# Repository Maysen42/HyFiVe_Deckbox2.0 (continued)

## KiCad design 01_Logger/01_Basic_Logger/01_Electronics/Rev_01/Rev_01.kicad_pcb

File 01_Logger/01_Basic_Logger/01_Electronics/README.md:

# Basic Logger - Electronics

The hardware is designed and can be modified in KiCad 7. Therefore the folder **/HyfiveLib** contains custom footprints and schematics for the projects below.

## Main PCB
The main PCB is designed to run the operations of the logger. It features an ESP32 as a micro controller and some peripheral components to integrate a wide range of sensors. To assemble a PCB for a logger follow the instructions of the [BOM.md](./BOM.md). The basic logger can implement sensors by

	- 3x I2C
	- 2x UART
	- 1x RS485

To select possible sensors to implement take a look into the subfolder [*../04_Sensors*](../04_Sensors/). The list can of course be extended. So far all sensors except the ones by BlueRobotics are connected with Molex PicoBlade connectors. How to connect each sensor in hardware is described in the sensor readme.

How to program the electronics after manufacturing is explained in the subfolder [*../03_Software*](../03_Software/).

A basic version of the PCB is shown in the image below.

<figure> 

   <figurecaption><a name="figure1">*Figure 1:*</a> *Main PCB inside the basic logger*</figurecaption>
</figure>

## Keller connector
  
One additional PCB, that is needed to implement a Keller 9LD pressure sensor, is given in **/KellerConnector**. The PCB can be soldered to the pins of the sensor and can then be directly connected to I2C1 (53261-0471) of the main PCB with a 4 pin Molex connector (15134-0402).

<figure> 

   <figurecaption><a name="figure2">*Figure 2:*</a> *Small PCB for interfacing the Keller pressure sensor*</figurecaption>
</figure>

## Battery

The power supply of the logger can be any battery pack that fits the case. We have user 12 LiPo (3,7 V, type 18650) cells in parallel (12P1S) with the connector Molex: 15136-0203. This fits to the power socket of the PCB (55935-0230).

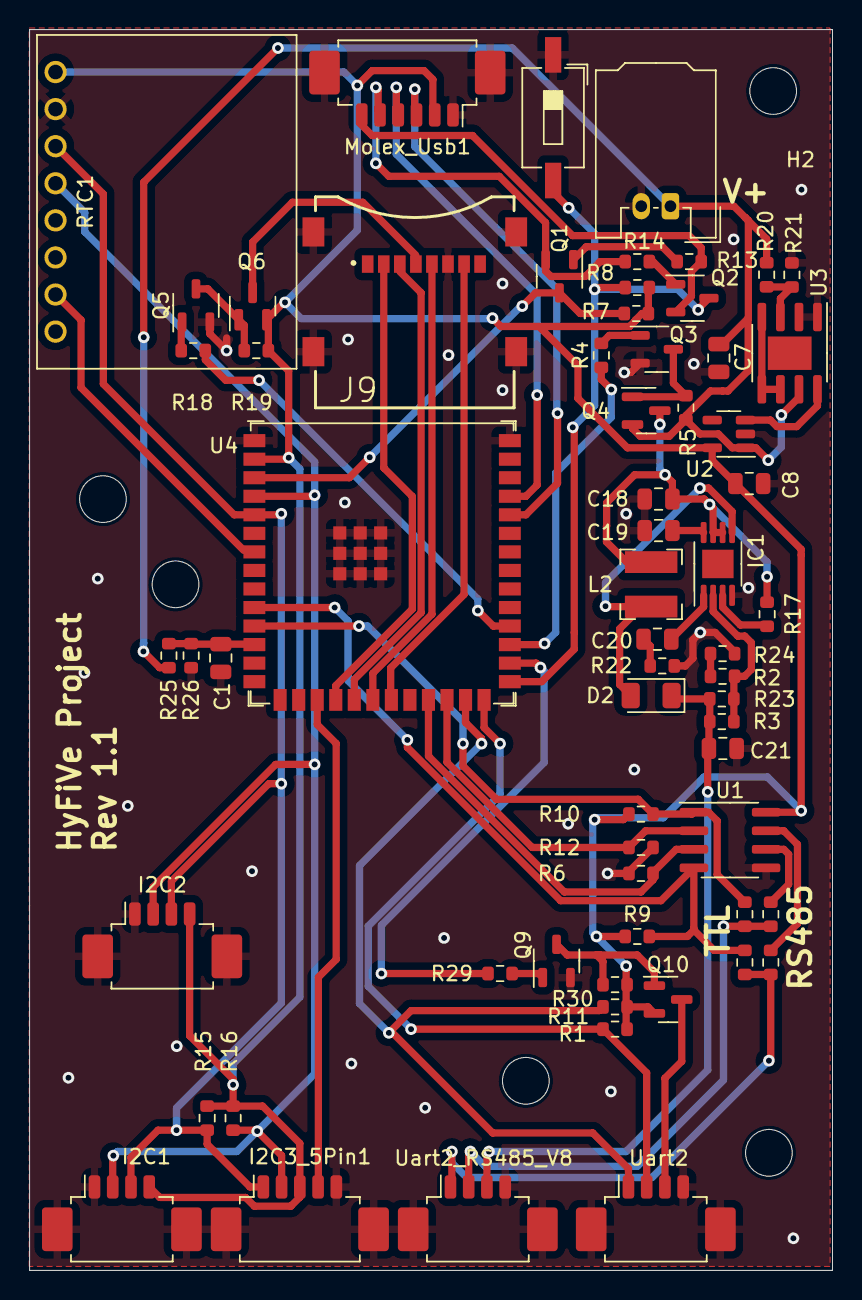
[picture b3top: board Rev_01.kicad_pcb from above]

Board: 2 copper layers, 55.0 x 85.0 mm, 69 parts (0 on the bottom side), 53 nets.

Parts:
C1, C19: 10n; C_0805_2012Metric
C7, C8: 1µ; C_0805_2012Metric
C18: 10µ; C_0805_2012Metric
C20: 2,2n; C_0805_2012Metric
C21: 4,7µ; C_0805_2012Metric
D2: D_Schottky; D_1206_3216Metric
H1, H2, H3: MountingHole; MountingHole_3.2mm_M3
H4, H5: MountingHole; MountingHole_3.2mm_M3_DIN965
I2C1, I2C2: Conn_01x04_MountingPin; Molex_PicoBlade_53261-0471_1x04-1MP_P1.25mm_Horizontal
I2C3_5Pin1: Conn_01x05_MountingPin; Molex_PicoBlade_53261-0571_1x05-1MP_P1.25mm_Horizontal
IC1: MP3213DH-LF-Z; MSOP-8-1EP_3x3mm_P0.65mm_EP1.95x2.15mm
J9: Micro_SD_Card; GCT_MEM2067-02-180-00-A_REVB
L2: 4,7µ; L_Bourns-SRN4018
Molex_Battery1: Conn_01x02; Molex_MicroClasp_55935-0230_1x02_P2.00mm_Horizontal
Molex_Usb1: Conn_01x06_MountingPin; Molex_PicoBlade_53261-0671_1x06-1MP_P1.25mm_Horizontal
Q1, Q2, Q3, Q5, Q9: SS8050-G; SOT-23-3
Q4, Q6, Q10: BSS83P; SOT-23
R1, R9, R10, R11: 100k; R_0603_1608Metric
R2, R24: 12k; R_0603_1608Metric
R3, R23: 470k; R_0603_1608Metric
R4, R5, R17, R18, R19, R22, R29, R30: 15k; R_0603_1608Metric
R6, R12, R15, R16: 1k; R_0603_1608Metric
R7, R8, R13, R14: 10k; R_0603_1608Metric
R20, R21, R25, R26: 1M; R_0603_1608Metric
R40, R41, R42, R43: 0; R_0603_1608Metric
RTC1: Conn_01x08; DS3231Module
SW1: SW_DIP_x01; SW_DIP_SPSTx01_Slide_6.7x4.1mm_W8.61mm_P2.54mm_LowProfile
U1: THVD14x9; SOIC-8_3.9x4.9mm_P1.27mm
U2: RT9080-33GJ5; SOT-23-5
U3: LTC1540; SOIC-8-1EP_3.9x4.9mm_P1.27mm_EP2.29x3mm
U4: ESP32-S3-WROOM-1; ESP32-S3-WROOM-1U
Uart2, Uart2_RS485_V8: Conn_01x04_MountingPin; Molex_PicoBlade_53261-0471_1x04-1MP_P1.25mm_Horizontal

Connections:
/3V3: C8.1, I2C1.4, I2C2.4, I2C3_5Pin1.3, Molex_Usb1.2, Q6.2 (S), Q10.2 (S), R1.1, R7.2, R8.2, R9.1, R10.1, R11.1, R15.2, R16.2, R19.1, R30.1, RTC1.1, U1.8 (VCC), U2.5 (VOUT), U4.2 (3V3)
/AnaIn: C1.1, R25.2, R26.1, U4.12 (GPIO8/TOUCH8/ADC1_CH7/SUBSPICS1)
/BoostEnable: R4.1, U4.29 (SPIIO7/GPIO36/FSPICLK/SUBSPICLK)
/CS_SD: J9.2 (DAT3/CD), U4.18 (GPIO10/TOUCH10/ADC1_CH9/FSPICS0/FSPIIO4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)
/DE485: R6.1, U1.3 (DE), U4.23 (GPIO21)
/DTR: Molex_Usb1.6, Q2.2, R13.1
/EN: Q1.3, R7.1, U4.3 (EN)
/EzoOff: I2C3_5Pin1.4, U4.17 (GPIO9/TOUCH9/ADC1_CH8/FSPIHD/SUBSPIHD)
/IO0: Q2.3, R8.1, SW1.2, U4.27 (GPIO0/BOOT)
/MISO: J9.7 (DAT0), U4.21 (GPIO13/TOUCH13/ADC2_CH2/FSPIQ/FSPIIO7/S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)
/MOSI: J9.3 (CMD), U4.19 (GPIO11/TOUCH11/ADC2_CH0/FSPID/FSPIIO5/S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)
/RE485: R12.1, U1.2 (RE), U4.24 (GPIO47/SPICLK_P/SUBSPICLK_P_DIFF)
/RTS: Molex_Usb1.5, Q1.2, R14.1
/RXD0: Molex_Usb1.3, U4.36 (U0RXD/GPIO44/CLK_OUT2)
/RtcInt: RTC1.7, U4.7 (GPIO7/TOUCH7/ADC1_CH6)
/SCK: J9.5 (CLK), U4.20 (GPIO12/TOUCH12/ADC2_CH1/FSPICLK/FSPIIO6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)
/SCL: I2C1.3, I2C2.3, I2C3_5Pin1.1, R15.1, RTC1.3, U4.5 (GPIO5/TOUCH5/ADC1_CH4)
/SDA: I2C1.2, I2C2.2, I2C3_5Pin1.2, R16.1, RTC1.4, U4.4 (GPIO4/TOUCH4/ADC1_CH3)
/SD_Enable: R18.1, U4.30 (SPIDQS/GPIO37/FSPIQ/SUBSPIQ)
/SensUartEnable: R29.1, U4.28 (SPIIO6/GPIO35/FSPID/SUBSPID)
/TXD0: Molex_Usb1.4, U4.37 (U0TXD/GPIO43/CLK_OUT1)
/Uart1Rx: R10.2, R42.1, U1.1 (R), U4.11 (GPIO18/U1RXD/ADC2_CH7/CLK_OUT3)
/Uart1Tx: R9.2, R40.1, U1.4 (D), U4.10 (GPIO17/U1TXD/ADC2_CH6)
/Uart2Rx: R1.2, U4.26 (GPIO45), Uart2.2
/Uart2Tx: R11.2, U4.25 (GPIO48/SPICLK_N/SUBSPICLK_N_DIFF), Uart2.1
/VBat: C7.1, Molex_Battery1.1, Q4.2 (S), R5.1, R20.1, R25.1, U2.1 (VIN), U3.7 (V+)
/VOxy: C21.1, D2.1 (K), R3.1, R23.1, Uart2_RS485_V8.3
GND: C1.2, C7.2, C8.2, C18.2, C19.2, C21.2, I2C1.1, I2C1.MP (MountPin), I2C2.1, I2C2.MP (MountPin), I2C3_5Pin1.5, I2C3_5Pin1.MP (MountPin), IC1.4 (GND), J9.6 (VSS), J9.9 (SHIELD), J9.10 (SHIELD), J9.11 (SHIELD), J9.12 (SHIELD), Molex_Battery1.2, Molex_Usb1.1, Molex_Usb1.MP (MountPin), Q3.2, Q5.2, Q9.2, R6.2, R12.2, R21.2, R22.2, R24.2, R26.2, RTC1.2, SW1.1, U1.5 (GND), U2.2 (GND), U3.1 (GND), U3.2 (V-), U4.1 (GND), U4.40 (GND), U4.41 (GND), Uart2.4, Uart2.MP (MountPin), Uart2_RS485_V8.4, Uart2_RS485_V8.MP (MountPin)
unnamed: C20.2, R22.1
unnamed: D2.2 (A), IC1.5 (SW), L2.2
unnamed: C20.1, IC1.1 (COMP)
unnamed: IC1.3 (EN), R17.2
unnamed: IC1.2 (FB), R2.1, R3.2, R23.2
unnamed: C18.1, IC1.6 (IN), IC1.7 (FSEL), L2.1, Q4.3 (D), R17.1
unnamed: C19.1, IC1.8 (SS)
unnamed: J9.4 (VDD), Q6.3 (D)
unnamed: Q1.1, R13.2
unnamed: Q2.1, R14.2
unnamed: Q3.1, R4.2
unnamed: Q3.3, Q4.1 (G), R5.2
unnamed: Q5.1, R18.2
unnamed: Q5.3, Q6.1 (G), R19.2
unnamed: Q9.1, R29.2
unnamed: Q10.3 (D), Uart2.3
unnamed: Q9.3, Q10.1 (G), R30.2
unnamed: R2.2, R24.1
unnamed: R43.1, U1.6 (A)
unnamed: R41.1, U1.7 (B)
unnamed: U2.3 (EN), U3.8
unnamed: R20.2, R21.1, U3.3 (+)
unnamed: U3.4 (-), U3.5 (HYST), U3.6 (REF)
unnamed: R40.2, R41.2, Uart2_RS485_V8.1
unnamed: R42.2, R43.2, Uart2_RS485_V8.2

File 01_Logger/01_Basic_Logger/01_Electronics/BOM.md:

Bil of Materials
================

# Electronics main PCB
  
To manufacture the electronic hardware of a logger order the PCB in **/Rev_01**. To assemble the PCB to your needs follow the instructions and the bill of materials in the tables below. The schematics and board design in **/Rev_01** provide additional information for the assembly.  

 **Note:** The connection between the hardware and software is very close in this embedded design. Understanding and testing the the hardware in detail is highly recommended before usage. GPIOs of the µC are in the code to switch components such as sensors and the SD card and can lead to errors in case of changes.
## Main components for PCB Rev_01


These are components needed in any case to run the microcontroller and his basic functions.

U3 is used to protect the power supply from deep discharge. Wit the combination of R22 and R21 it will turn everything off, when the battery is lower than 3.55 V. If this is not needed, bridge pin 7 & 8 of U3.

**Note:** when using Blue Robotics sensors, I2C1 and I2C2 should be replaced with BM04B-GHS-TBT to connect them easily.
|Reference|Amount|Value|Footprint|Manufacturer Part Number|
| :---: | :---: | :---: | :---: | :---: |
|C1|1|10n|Capacitor_SMD:C_0805_2012Metric||
|C7, C8|2|1µ|Capacitor_SMD:C_0805_2012Metric||
|H1, H2, H3|3|MountingHole|MountingHole:MountingHole_3.2mm_M3||
|H4, H5|2|MountingHole|MountingHole:MountingHole_3.2mm_M3_DIN965||
|I2C1, I2C2|2|Conn_01x04_MountingPin|Connector_Molex:Molex_PicoBlade_53261-0471_1x04-1MP_P1.25mm_Horizontal|53261-0471|
|I2C3_5Pin1|1|Conn_01x05_MountingPin|Connector_Molex:Molex_PicoBlade_53261-0571_1x05-1MP_P1.25mm_Horizontal|53261-0571|
|J9|1|Micro_SD_Card|Hyfive:GCT_MEM2067-02-180-00-A_REVB|MEM2067-02-180-00-A|
|Molex_Battery1|1|Conn_01x02|Connector_Molex:Molex_MicroClasp_55935-0230_1x02_P2.00mm_Horizontal|55935-0230|
|Molex_Usb1|1|Conn_01x06_MountingPin|Connector_Molex:Molex_PicoBlade_53261-0671_1x06-1MP_P1.25mm_Horizontal|53261-0671|
|Q1, Q2, Q5|3|SS8050-G|Package_TO_SOT_SMD:SOT-23-3|SS8050-G|
|Q6|1|BSS83P|Package_TO_SOT_SMD:SOT-23|MMFTP84|
|R7, R8, R13, R14|4|10k|Resistor_SMD:R_0603_1608Metric||
|R15, R16|2|1k|Resistor_SMD:R_0603_1608Metric||
|R18, R19|2|15k|Resistor_SMD:R_0603_1608Metric||
|R20|1|2M2|Resistor_SMD:R_0603_1608Metric||
|R21, R25, R26|3|1M|Resistor_SMD:R_0603_1608Metric||
|RTC1|1|Conn_01x08|Hyfive:DS3231Module|3013|
|SW1|1|SW_DIP_x01|Button_Switch_SMD:SW_DIP_SPSTx01_Slide_6.7x4.1mm_W8.61mm_P2.54mm_LowProfile|434111025826|
|U2|1|RT9080-33GJ5|Package_TO_SOT_SMD:SOT-23-5|RT9080-33GJ5|
|U3|1|LTC1540|Package_SO:SOIC-8-1EP_3.9x4.9mm_P1.27mm_EP2.29x3mm|LTC1540CS8#TRPBF|
|U4|1|ESP32-S3-WROOM-1|PCM_Espressif:ESP32-S3-WROOM-1U|ESP32-S3-WROOM-1U-N16R2|

## Optional components according to the used sensors

### UART1 with boost converter (13V) and optional RS485


These components enable a higher supply voltage for one sensor. The voltage can be adjusted bythe setup of R3, R23, R2 and R24.
|Reference|Amount|Value|Footprint|Manufacturer Part Number|
| :---: | :---: | :---: | :---: | :---: |
|C18|1|10µ|Capacitor_SMD:C_0805_2012Metric|TMK212BBJ106KG8T|
|C19|1|10n|Capacitor_SMD:C_0805_2012Metric||
|C20|1|2,2n|Capacitor_SMD:C_0805_2012Metric||
|C21|1|4,7µ|Capacitor_SMD:C_0805_2012Metric|GCM21BC71E475KE36L|
|D2|1|D_Schottky|Diode_SMD:D_1206_3216Metric|CD1206-B240|
|IC1|1|MP3213DH-LF-Z|Package_SO:MSOP-8-1EP_3x3mm_P0.65mm_EP1.95x2.15mm|MP3213DH-LF-Z|
|L2|1|4,7µ|Inductor_SMD:L_Bourns-SRN4018|SRN4018-4R7M|
|Q3|1|SS8050-G|Package_TO_SOT_SMD:SOT-23-3|SS8050-G|
|Q4|1|BSS83P|Package_TO_SOT_SMD:SOT-23|MMFTP84|
|R2, R24|2|12k|Resistor_SMD:R_0603_1608Metric||
|R3, R23|2|470k|Resistor_SMD:R_0603_1608Metric||
|R4, R5, R22|3|15k|Resistor_SMD:R_0603_1608Metric||
|R9, R10|2|100k|Resistor_SMD:R_0603_1608Metric||
|Uart2_RS485_V8|1|Conn_01x04_MountingPin|Connector_Molex:Molex_PicoBlade_53261-0471_1x04-1MP_P1.25mm_Horizontal|53261-0471|

### UART1 or RS485


For using UART1 use
|Reference|Amount|Value|Footprint|Manufacturer Part Number|
| :---: | :---: | :---: | :---: | :---: |
|R40, R42|2|0|Resistor_SMD:R_0603_1608Metric||


For using RS485 use
|Reference|Amount|Value|Footprint|Manufacturer Part Number|
| :---: | :---: | :---: | :---: | :---: |
|R6, R12|2|1k|Resistor_SMD:R_0603_1608Metric||
|R41, R43|2|0|Resistor_SMD:R_0603_1608Metric||
|U1|1|THVD14x9|Package_SO:SOIC-8_3.9x4.9mm_P1.27mm|THVD1429DT|

### UART2, 3.3V


UART2 runs with 3.3V and can be switched off by a high side switch.
|Reference|Amount|Value|Footprint|Manufacturer Part Number|
| :---: | :---: | :---: | :---: | :---: |
|Q9|1|SS8050-G|Package_TO_SOT_SMD:SOT-23-3|SS8050-G|
|Q10|1|BSS83P|Package_TO_SOT_SMD:SOT-23|MMFTP84|
|R1, R11|2|100k|Resistor_SMD:R_0603_1608Metric||
|R29, R30|2|15k|Resistor_SMD:R_0603_1608Metric||
|Uart2|1|Conn_01x04_MountingPin|Connector_Molex:Molex_PicoBlade_53261-0471_1x04-1MP_P1.25mm_Horizontal|53261-0471|

# External components to implement the sensors and power the system

|Reference|Amount|Function|Manufacturer Part Number|
| :---: | :---: | :---: | :---: |
|Molex connector I2C|4|Connect 4 pin I2C sensor|Molex: 15134-0402|
|Molex connector I2C|1|Connect 5 pin I2C sensor|Molex: 15134-0502|
|Molex connector UART|1|Connect programmer|Molex: 15134-0602|
|Molex connector V+|1|Connect power|Molex: 15136-0203|
|Molex Antenna|1|Improve connection of ESP|Molex: 47950-0011|
|UART Progammer|1|Programm the ESP32 with code|Digilent: 410-212|

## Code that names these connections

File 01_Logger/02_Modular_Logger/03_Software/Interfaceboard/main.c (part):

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    P1SEL0 |= BIT2 | BIT3;                  // it is 1.2: UCB0_SDA and 1.3:UCB0_SCL

    // I2C Master pins. This interface is connecting sensor on I2C Board
    P3SEL0 |= BIT2 | BIT6;                  // I2C pins - it is 3.2: UCB1_SDA and 3.6:UCB1_SCL

    P1DIR |= BIT1;
    P1OUT |= BIT1;
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

    // I2C Adresse
        //configure pullups on Dipswitches Pins 0-4 which is Signals ADDR_B0 - ADDR_B4 on Board
            //ADDR_B0 --> P3.4
            //ADDR_B1 --> P2.3
            //ADDR_B2 --> P3.3
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
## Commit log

2024-08-08 initial commit
    Initial commit of the HyFiVe project
2024-08-09 added missing images
    Images for mechanics of deck box were missing
2024-09-06 Add modular logger files and change structure accordingly
2024-09-09 Initial Commit of Interfaceboard Software
2024-09-17 edited logger readmes and added pictures
2024-09-17 Rename logger_modular.JPG to logger_modular.jpg
2024-09-17 Rename electronic_mounting_modeled.PNG to electronic_mounting_modeled.png
2024-09-17 Minor fix for image positioning
2024-09-17 Update README.md
    trying to fix image positioning
2024-09-17 Test
2024-09-18 fixed some bugs
2024-09-18 Update main readme (introduction)
    and finally fixed issue with side-by-side positioning of figures in other readmes
2024-09-19 updated readmes (main plus logger)
2024-09-20 readmes updated (config update of logger, sensors and deckbox)
2024-09-23 updated readmes (deckbox; introducing bi-directional communication)
2024-09-24 updated readmes (server)
2024-09-24 updating readmes (minor fix)
2024-09-26 additional CAD-Files
    Adding F3D, STEP and PNG-Files for all relevant mechanical parts.
2024-09-30 update README.md to 02_Modular_Logger\01_Electronics
2024-10-01 update README.md to 02_Modular_Logger\03_Software
2024-10-10 firmware update 0.6
2024-10-11 Create nodered_all_flows_20241011.json
    Log content of the logger is also transmitted
2024-10-11 update Electronics for Modular_Logger
2024-10-11 folder structure adjusted
2024-10-14 Assembly Instructions 02_Modular_Logger
2024-10-14 fixed db query for vessels in deployments
2024-10-23 Update nodered_all_flows_20241011.json
    "Prepare data" and "Prepare Header" are connected to the store data
2024-11-07 firmware update V0.7
    Previously, if the battery was discharged below 5%, errors occurred during charging due to undervoltage
    This issue has been resolved with the current firmware update
2024-11-11 Charging process adjusted up to 100%, as battery-dependent variations are possible
    FW: 0.71
2024-11-11 fixed some path to python script bug
2024-11-20 added OTA (Over-The-Air) firmware update feature
    Firmware Update v0.80
    - Added OTA firmware update feature
    - Enhanced code comments
    - Optimized function behavior
    - Implemented Node-RED flow for OTA firmware updates (nodered_all_flows_20241120.json)
2024-12-10 The WiFi connection problems have been resolved. firmware update V0.81
2025-02-04 Update DeckunitV1_BOM.csv
    Some parts were replaced by better available equivalent parts from other manufacturers
2025-02-24 undervoltageProtection added
2025-07-07 Update README.md
    Update instruction for assembly of deckbox 2.0
2025-07-07 Update README.md
    corrections in formatting
2025-07-08 Update README.md
    minor additions
2025-07-08 added images
    added images for mounting antennas
2025-07-08 test changed images
2025-07-11 images for updated instructions
2025-07-11 Update README.md
    mounting antenna
2025-07-11 Update README.md
    finished top part
2025-07-11 Rename config_1_overview.PNG to config_1_overview.png
2025-07-15 Update README.md
    finished part about router
2025-07-15 add images to instructions
2025-07-15 added images of cage
2025-07-17 Update README.md
    Update BOM and Tools
2025-07-18 Update README.md
    new pictures fo weipu and gluing with sikaflex
2025-07-18 Update README.md
    fix format
2025-07-18 new picturs and updated holes drawing
2025-07-21 intructions for USB and Molex Plug
2025-07-21 some small fixes
2025-07-22 typos
2025-07-22 update layout
2025-07-22 add instructions for raspi case
2025-07-23 general alarm time update
2025-07-23 typos, new images for pcb connection
2025-07-23 new images for pcb connection
2025-07-23 correction on images
2025-07-25 Check and add missing GTINs
2025-07-25 typo
2025-07-25 CAD-Files updated
    Updated all CAD files to new Deckbox Version
2025-07-25 deleting old images
    Deleted old images
2025-07-25 add wiring diagram
2025-07-25 Deckbox Upgrade 2.0 to IP67 (#2)
    Update instruction for assembly of deckbox 2.0
    * Update README.md
    * added images for updated instructions
    * Update BOM and Tools
    * intructions for USB and Molex Plug
    Updated BOM.xlsx
